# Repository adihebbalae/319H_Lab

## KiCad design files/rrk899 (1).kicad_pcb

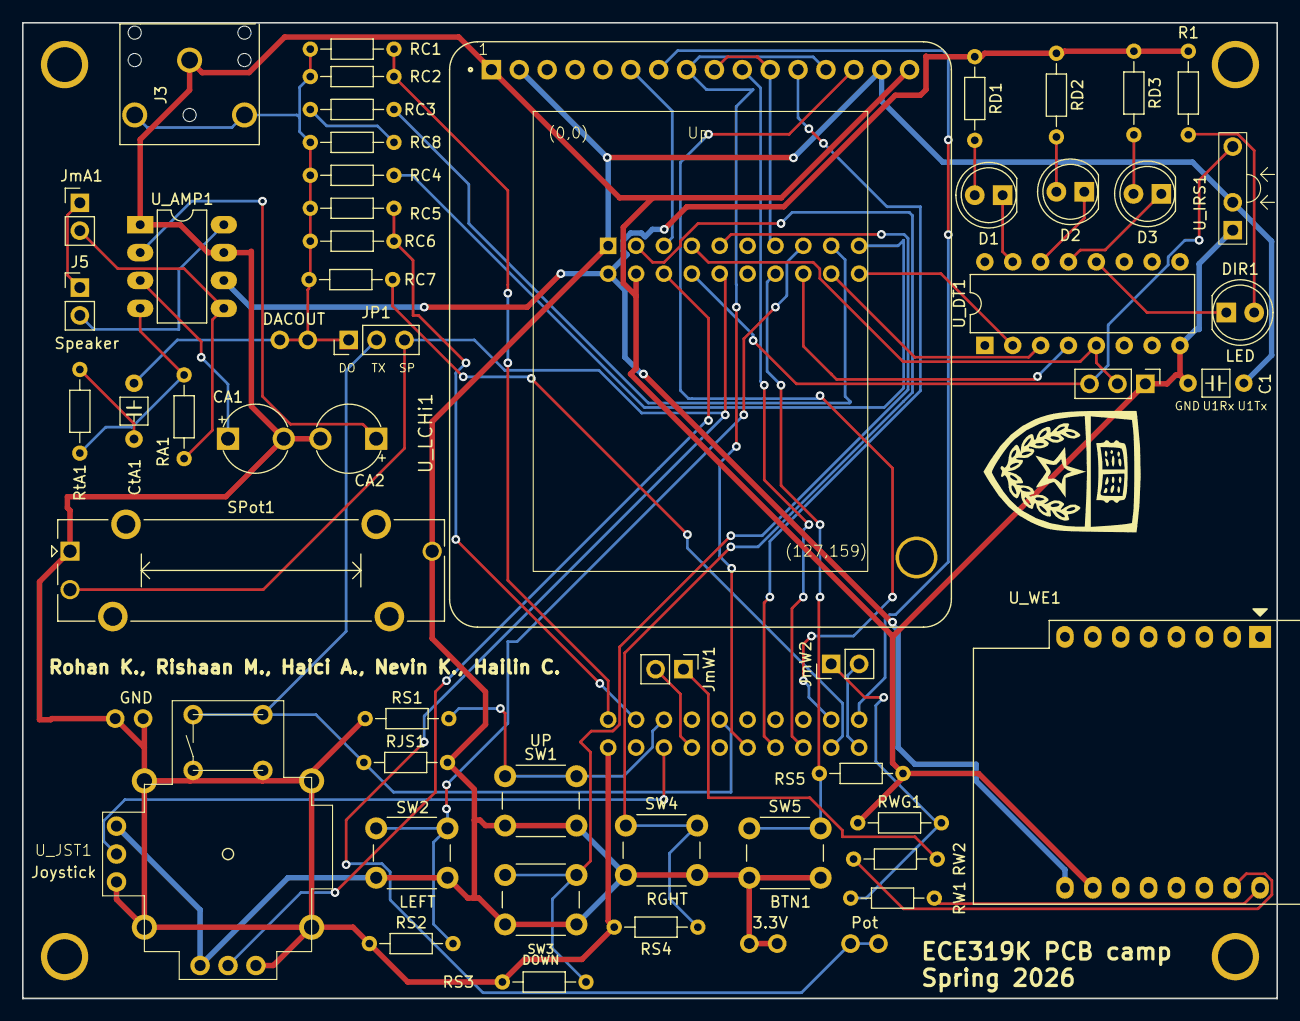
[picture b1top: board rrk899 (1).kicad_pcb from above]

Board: 2 copper layers, 114.3 x 88.9 mm, 59 parts (1 on the bottom side), 52 nets.

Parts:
C1: 0.1uF; C_Axial_200mil
CA1: 1uF; CP_Radial_Tantal200mil
CA2: 4.7uF; CP_Radial_Tantal200mil
CtA1: 0.1uF; C_Axial_200mil
D1, D2, D3: LED; LED_D5.0mm
DIR1: LED; LED_D5.0mm
H1, H2, H3, H4: MountingHole_4_40
J1: DACOUT; Testpoint_1x02_P2.54mm
J2: GND; Testpoint_1x02_P2.54mm
J3: AudioJack; Jack_3.5mm_CUI_SJ1-3523N_Horizontal
J4: Pot; Testpoint_1x02_P2.54mm
J5: Speaker; PinHeader_1x02_P2.54mm_Vertical
J6: UART1; PinHeader_1x03_P2.54mm_Vertical
JP1: TExaS; PinHeader_1x03_P2.54mm_Vertical
JmA1: Jumper_2_Open; PinHeader_1x02_P2.54mm_Vertical
JmW1, JmW2: Jumper_2_Open; PinHeader_1x02_P2.54mm_Vertical
R1: 220; R_Axial_DIN0204_L3.6mm_D1.6mm_P7.62mm_Horizontal
RA1: 20k; R_Axial_DIN0204_L3.6mm_D1.6mm_P7.62mm_Horizontal
RC1, RC2, RC3, RC4, RC8: 1.5k; R_Axial_DIN0204_L3.6mm_D1.6mm_P7.62mm_Horizontal
RC5, RC6, RC7: 12k; R_Axial_DIN0204_L3.6mm_D1.6mm_P7.62mm_Horizontal
RD1, RD2, RD3: 220; R_Axial_DIN0204_L3.6mm_D1.6mm_P7.62mm_Horizontal
RJS1: 10k; R_Axial_DIN0204_L3.6mm_D1.6mm_P7.62mm_Horizontal
RS1, RS2, RS3, RS4, RS5: 10k; R_Axial_DIN0204_L3.6mm_D1.6mm_P7.62mm_Horizontal
RW1: 1k; R_Axial_DIN0204_L3.6mm_D1.6mm_P7.62mm_Horizontal
RW2: 220; R_Axial_DIN0204_L3.6mm_D1.6mm_P7.62mm_Horizontal
RWG1: 2k; R_Axial_DIN0204_L3.6mm_D1.6mm_P7.62mm_Horizontal
RtA1: 10k; R_Axial_DIN0204_L3.6mm_D1.6mm_P7.62mm_Horizontal
SPot1: PTA2043; PTA2043pot
SW1: UP; SW_PUSH_6mm
SW2: LEFT; SW_PUSH_6mm
SW3: DOWN; SW_PUSH_6mm
SW4: RGHT; SW_PUSH_6mm
SW5: BTN1; SW_PUSH_6mm
TP1: 3.3V; Testpoint_1x02_P2.54mm
U_AMP1: MCP34119P; DIP-8_W7.62mm_LongPads
U_DT1: ULN2003B; DIP-16_W7.62mm
U_IRS1: TSOP31438
U_JST1: Joystick; SparkfunJoystick
U_LCHi1: HiLetGo_ST7735R; hiletgo_st7735r
U_MC1: LP-MSPM0G3507; ti_LP_MSPM0G3507
U_WE1: WEMOS_D1_mini; WEMOS_D1_mini_light

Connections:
+3V3: C1.1, RJS1.2, SPot1.3, SW1.2, SW2.2, SW3.2, SW4.2, SW5.2, TP1.1 (A), TP1.2 (B), U_IRS1.2 (Vs), U_JST1.3 (V+), U_JST1.4 (H+), U_LCHi1.2 (VCC), U_LCHi1.15 (LED+), U_MC1.J1_1 (+3.3V)
+5V: R1.1, RD1.1, RD2.1, RD3.1, U_AMP1.6 (Vcc), U_MC1.J3_1 (+VBUS), U_WE1.9 (5V)
DACOUT: CtA1.1, J1.1 (A), J1.2 (B), J3.R (ring), J3.T (tip), JP1.1 (A), RC1.1, RC2.1, RC4.1, RC5.1, RC6.1, RC7.1, RC8.1
Dri5: DIR1.1 (K), U_DT1.12 (5C)
GND: C1.2, CA1.2, CA2.2, J2.1 (A), J2.2 (B), J3.S (sleeve), J6.1 (A), RS1.2, RS2.2, RS3.2, RS4.2, RS5.2, RWG1.1, SPot1.1, U_AMP1.1 (CD), U_AMP1.7 (GND), U_DT1.8 (E), U_IRS1.1 (Gnd), U_JST1.1 (V-), U_JST1.6 (H-), U_JST1.7 (M1), U_JST1.8 (M2), U_JST1.9 (M3), U_JST1.10 (M4), U_JST1.11 (SEL-), U_LCHi1.1 (GND), U_LCHi1.16 (LED-), U_MC1.J2_1 (GND), U_MC1.J3_2 (GND), U_WE1.10 (GND)
unnamed: CtA1.2, RtA1.2
unnamed: D1.2 (A), RD1.2
unnamed: D1.1 (K), U_DT1.15 (2C)
unnamed: D2.2 (A), RD2.2
unnamed: D2.1 (K), U_DT1.14 (3C)
unnamed: D3.2 (A), RD3.2
unnamed: D3.1 (K), U_DT1.13 (4C)
unnamed: DIR1.2 (A), R1.2
unnamed: J5.1, JmA1.1 (A)
unnamed: JmA1.2 (B), RA1.1, U_AMP1.5 (VO1)
unnamed: JmW1.1 (A), RW2.1
unnamed: JmW2.1 (A), RW1.2, RWG1.2
unnamed: RC3.1, RC8.2
unnamed: CA1.1, U_AMP1.3 (FC1)
unnamed: CA2.1, U_AMP1.2 (FC2)
unnamed: RA1.2, RtA1.1, U_AMP1.4 (VIN)
unnamed: J5.2, U_AMP1.8 (VO2)
unnamed: RW2.2, U_WE1.15 (RX)
unnamed: RW1.1, U_WE1.16 (TX)
PA8: J6.2 (B), U_DT1.5 (5B), U_MC1.J1_4 (PA8)
PA12: U_LCHi1.14 (SDC_CS), U_MC1.J4_9 (PA12)
PA13: U_LCHi1.7 (TFTDC), U_MC1.J4_10 (PA13)
PA15: U_DT1.2 (2B), U_MC1.J3_10 (PA15)
PA16: U_DT1.3 (3B), U_MC1.J3_9 (PA16)
PA17: U_DT1.4 (4B), U_MC1.J3_8 (PA17)
PA22: J6.3 (C), U_IRS1.3 (Out), U_MC1.J3_4 (PA22)
PA24: RS5.1, SW5.1, U_MC1.J3_7 (PA24)
PA25: RS4.1, SW4.1, U_MC1.J1_2 (PA25)
PA26: RS3.1, SW3.1, U_MC1.J1_5 (PA26)
PA27: RS2.1, SW2.1, U_MC1.J1_8 (PA27)
PA28: RS1.1, SW1.1, U_MC1.J4_3 (PA28)
PB0: RC7.2, U_MC1.J2_9 (PB0)
PB1: RC5.2, RC6.2, U_MC1.J4_2 (PB1)
PB2: RC3.2, U_MC1.J1_9 (PB2)
PB3: RC4.2, U_MC1.J1_10 (PB3)
PB4: RC1.2, RC2.2, U_MC1.J4_1 (PB4)
PB6: U_LCHi1.10 (TFT_CS), U_MC1.J2_8 (PB6)
PB7: U_LCHi1.12 (SDC_MISO), U_MC1.J2_7 (PB7)
PB8: U_LCHi1.8 (TFTMOSI), U_LCHi1.13 (SDC_MOSI), U_MC1.J2_6 (PB8)
PB9: U_LCHi1.9 (TFTSCK), U_LCHi1.11 (SDCSCK), U_MC1.J1_7 (PB9)
PB15: JmW1.2 (B), U_MC1.J2_4 (PB15)
PB16: JmW2.2 (B), U_MC1.J2_10 (PB16)
PB17: U_JST1.2 (Vert), U_MC1.J2_3 (PB17)
PB18: J4.1 (A), J4.2 (B), JP1.3 (B), SPot1.2, U_MC1.J3_5 (PB18)
PB19: U_JST1.5 (Hori), U_MC1.J3_3 (PB19)
PB20: JP1.2 (C), RJS1.1, U_JST1.12 (SEL+), U_MC1.J4_5 (PB20)
PB23: U_LCHi1.6 (RESET), U_MC1.J1_3 (PA9/PB23)

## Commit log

2026-03-30 Add SlidePot class with ADC initialization and methods
2026-03-30 Refactor ADC initialization and sampling code
2026-03-31 Create lab7Main
2026-04-01 Update lab7Main
2026-04-17 Add new file 'e' with a single character
2026-04-17 Rename BusyWait.s to files/BusyWait.s
2026-04-17 Rename FIFO2.cpp to files/FIFO2.cpp
2026-04-17 Moved files
2026-04-17 Initial commit: Lab9H source files
2026-04-20 Create e
2026-04-23 Updated file
